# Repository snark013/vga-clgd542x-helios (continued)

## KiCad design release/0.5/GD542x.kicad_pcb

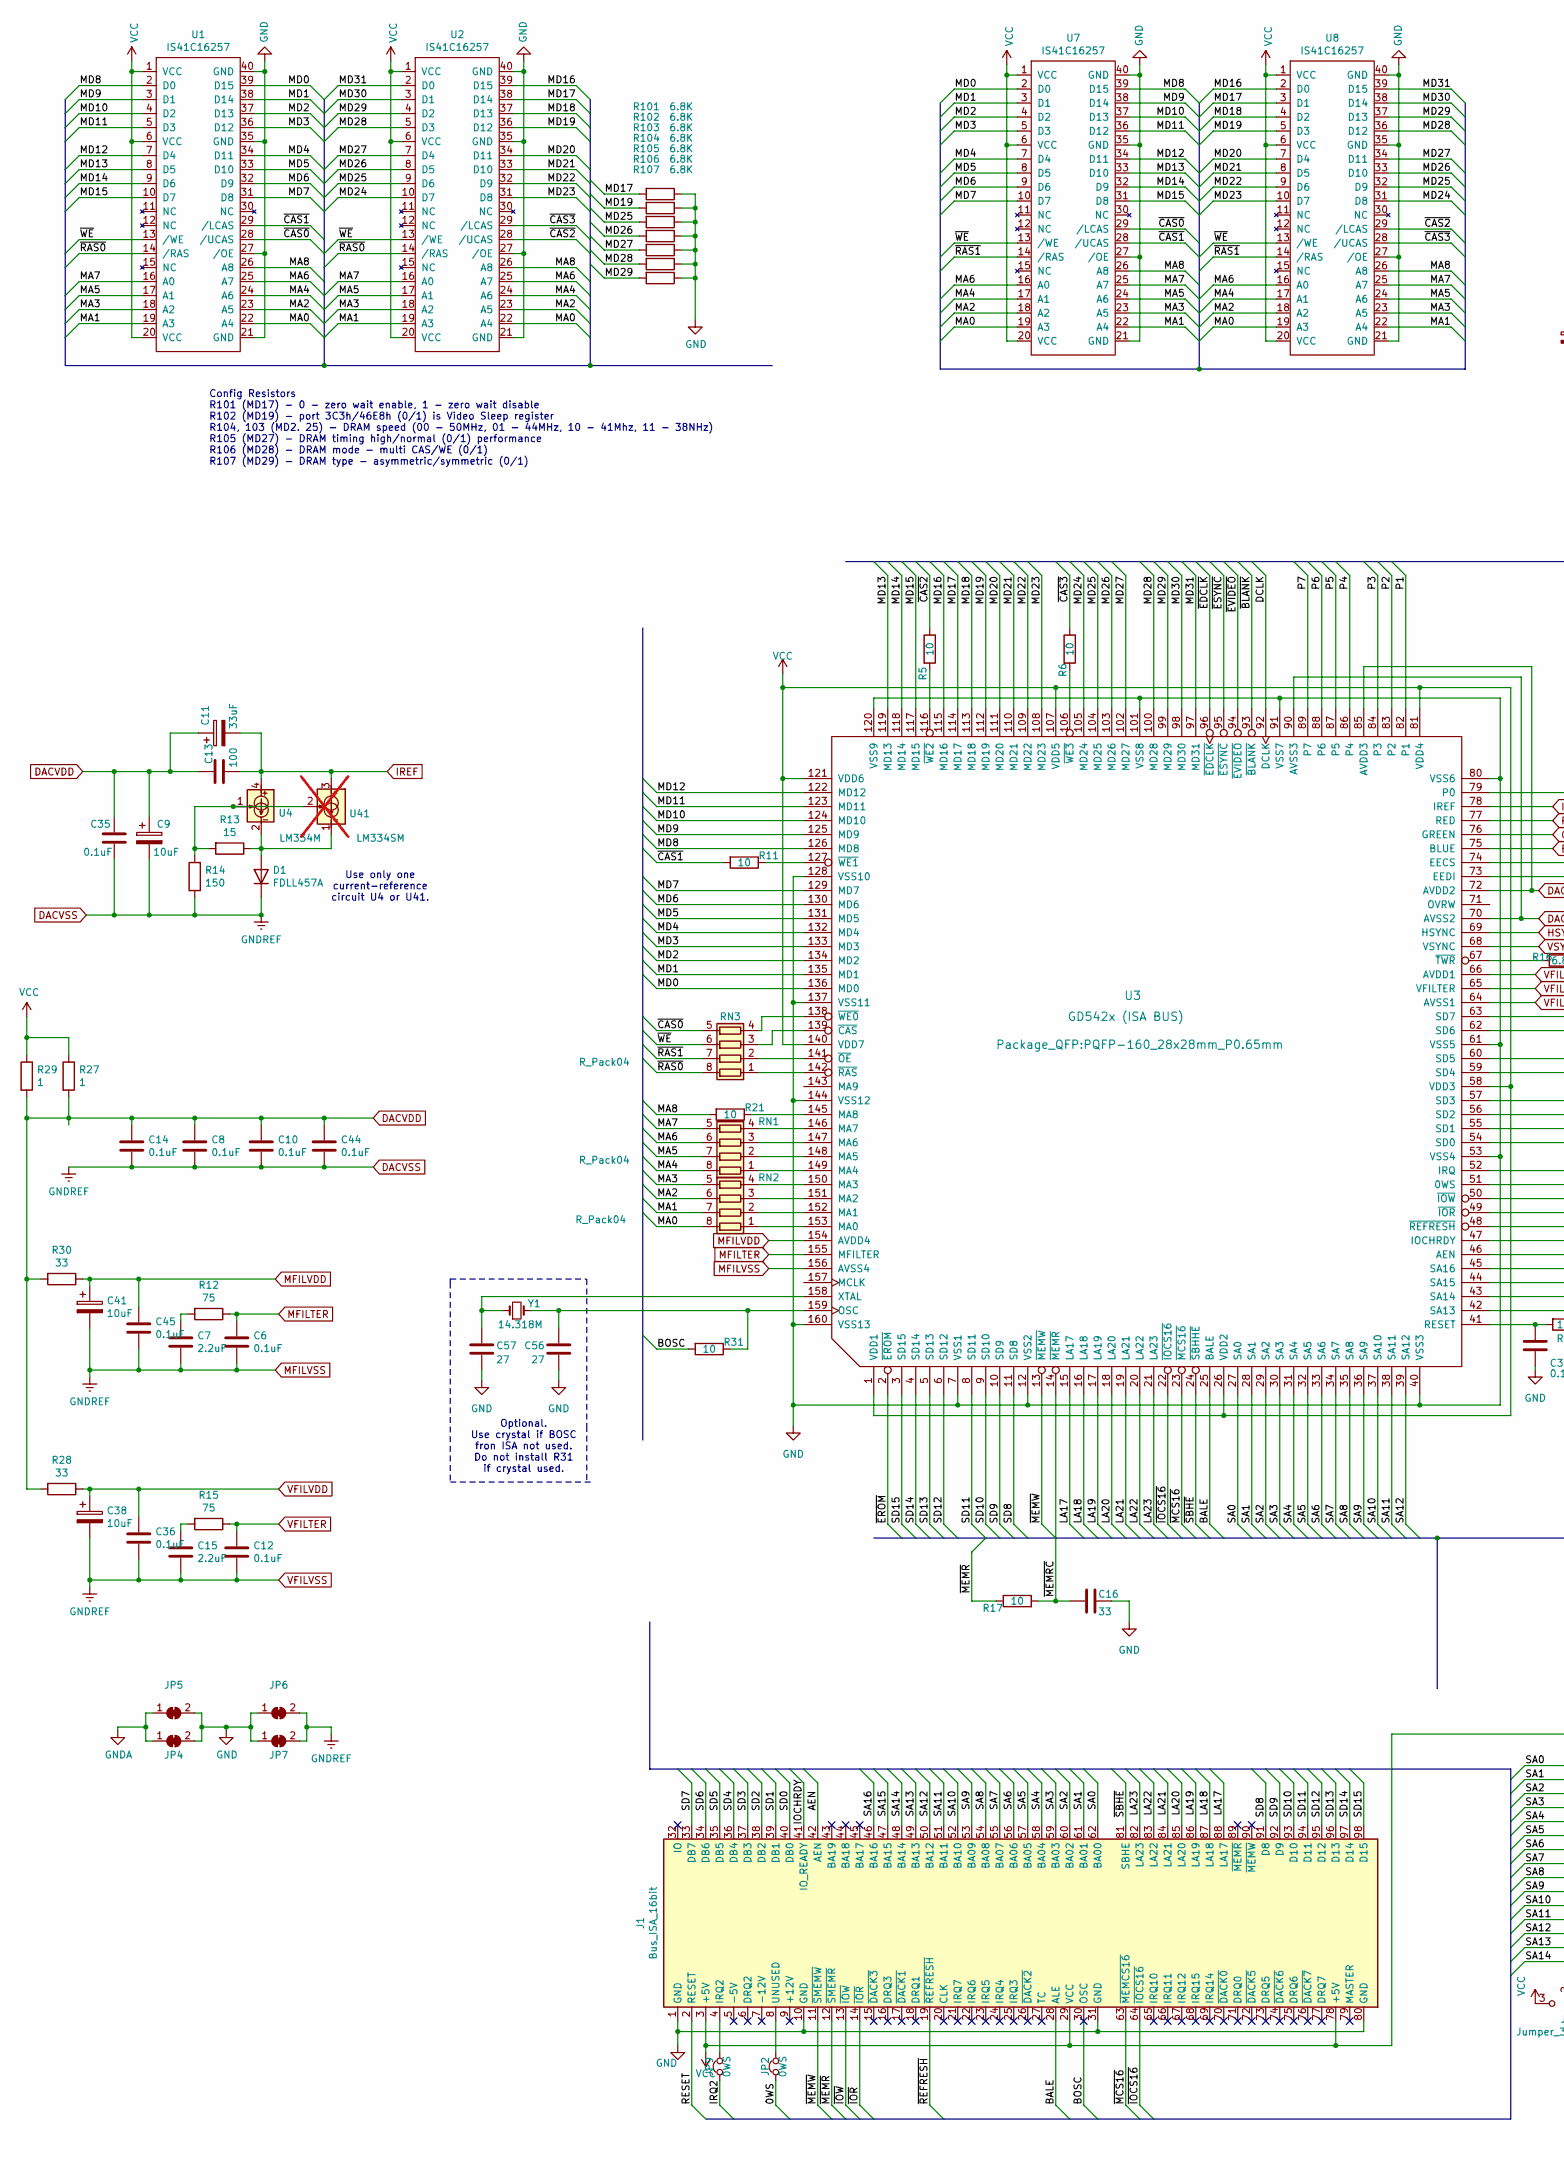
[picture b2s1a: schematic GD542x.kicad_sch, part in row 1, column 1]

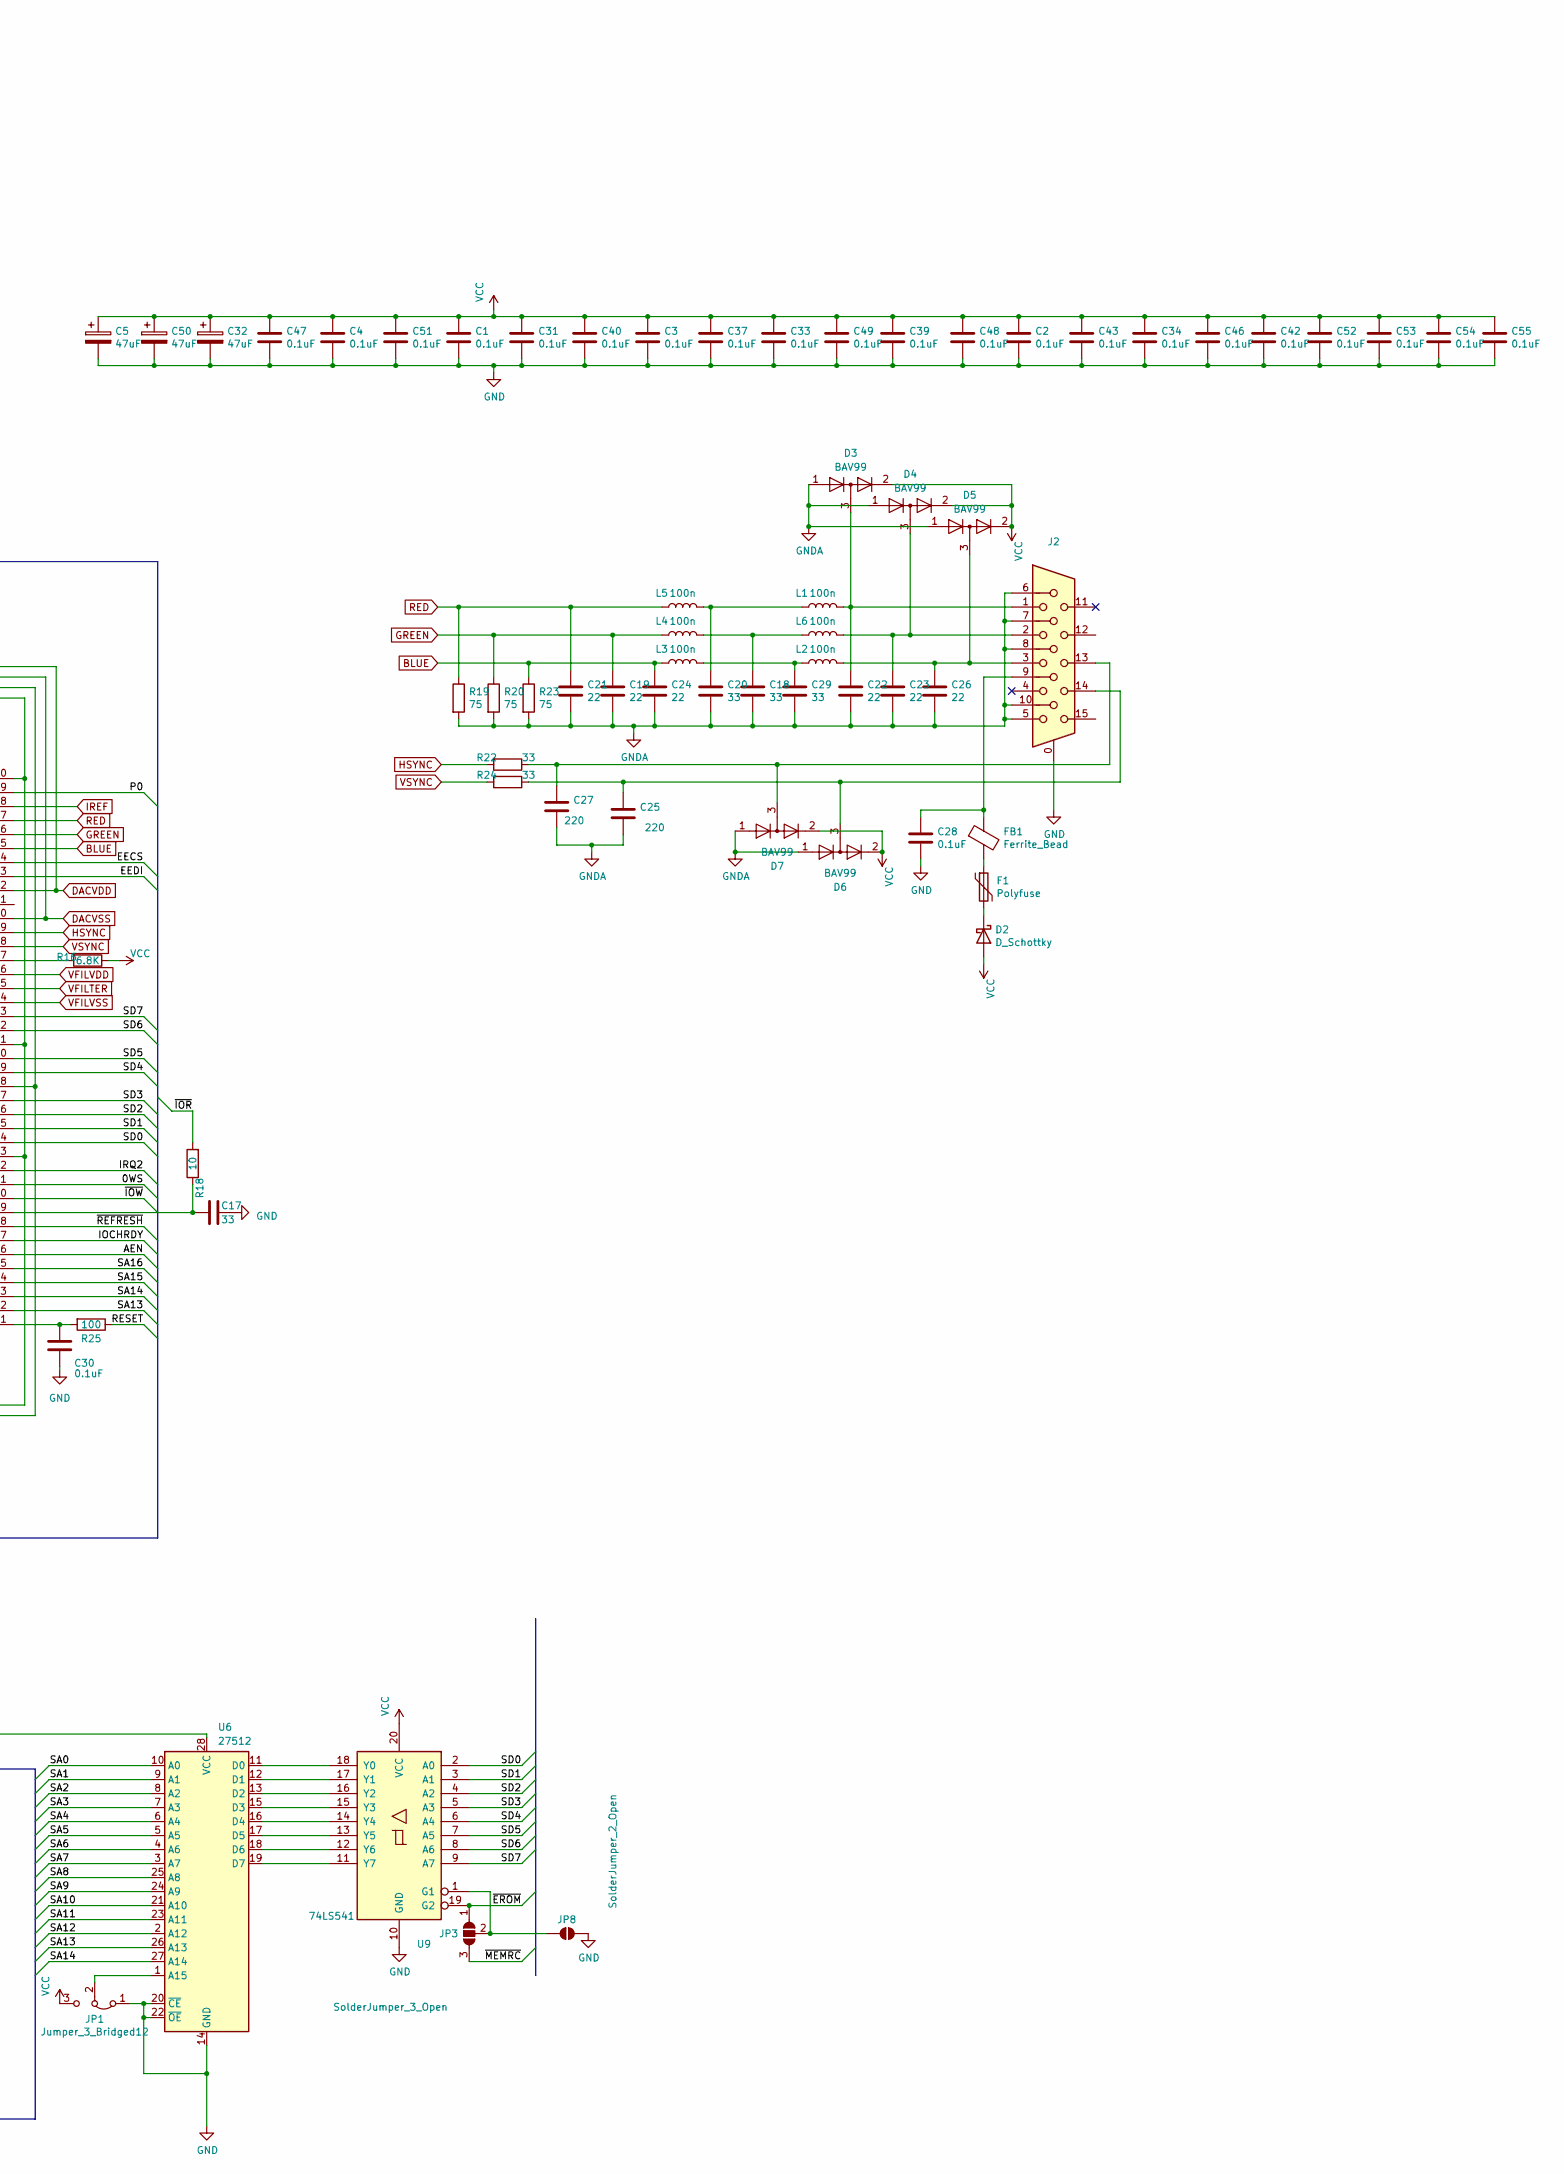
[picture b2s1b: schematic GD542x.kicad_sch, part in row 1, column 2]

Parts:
C1, C2, C3, C4, C6, C8, C10, C12, C14, C28, C30, C31, C33, C34, C35, C36, C37, C39, C40, C42, C43, C44, C45, C46, C47, C48, C49, C51, C52, C53, C54, C55: 0.1uF; C_0603_1608Metric
C5, C32, C50: 47uF; CP_EIA-3216-18_Kemet-A
C7, C15: 2.2uF; C_0603_1608Metric
C9: 10uF; CP_EIA-3216-18_Kemet-A
C11: 33uF; CP_EIA-3216-18_Kemet-A
C13: 100; C_0603_1608Metric
C16, C17, C18, C20, C29: 33; C_0603_1608Metric
C19, C21, C22, C23, C24, C26: 22; C_0603_1608Metric
C25, C27: 220; C_0603_1608Metric
C38, C41: 10uF; CP_EIA-3216-18_Kemet-A_Pad1.58x1.35mm_HandSolder
C56, C57: 27; C_0603_1608Metric
D1: FDLL457A; D_MiniMELF_Handsoldering
D2: D_Schottky; D_MELF-RM10_Universal_Handsoldering
D3, D4, D5, D6, D7: BAV99; SOT-23
F1: Polyfuse; Fuse_0805_2012Metric_Pad1.15x1.40mm_HandSolder
FB1: Ferrite_Bead; L_0805_2012Metric_Pad1.15x1.40mm_HandSolder
J1: Bus_ISA_16bit; BUS_AT
J2: DB15_Female_HighDensity_MountingHoles; DSUB-15-HD_Female_Horizontal_P2.29x1.98mm_EdgePinOffset3.03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
JP1: Jumper_3_Bridged12; PinHeader_1x03_P2.54mm_Vertical
JP2, JP9: 0WS; PinHeader_1x02_P2.54mm_Vertical
JP3: SolderJumper_3_Open; SolderJumper-3_P1.3mm_Open_RoundedPad1.0x1.5mm
JP4, JP5, JP6, JP7: SolderJumper_2_Bridged; NonSolderJumper-2_P1.3mm_Bridged2Bar_Pad1.0x1.5mm
JP8: SolderJumper_2_Open; SolderJumper-2_P1.3mm_Open_RoundedPad1.0x1.5mm
L1, L2, L3, L4, L5, L6: 100n; L_0805_2012Metric_Pad1.15x1.40mm_HandSolder
R5, R6, R11, R21: 10; R_0402_1005Metric_Pad0.72x0.64mm_HandSolder
R12, R15, R19, R20, R23: 75; R_0603_1608Metric
R13: 15; R_0603_1608Metric
R14: 150; R_0603_1608Metric
R16, R101, R102, R103, R104, R105, R106, R107: 6.8K; R_0603_1608Metric
R17, R18, R31: 10; R_0603_1608Metric
R22, R24, R28, R30: 33; R_0603_1608Metric
R25: 100; R_0603_1608Metric
R27, R29: 1; R_0603_1608Metric
RN1, RN2, RN3: R_Pack04; R_Array_Concave_4x0603
U1, U2, U7, U8: IS41C16257; SOJ-40-Socket-LongPads
U3: GD542x (ISA BUS); PQFP-160_28x28mm_P0.65mm
U4: LM334M; SOIC-8_3.9x4.9mm_P1.27mm
U6: 27512; DIP-28_W15.24mm
U9: 74LS541; CERDIP-20_W7.62mm_SideBrazed
U41: LM334SM; SOIC-8_3.9x4.9mm_P1.27mm; not fitted
Y1: 14.318M; Crystal_SMD_5032-2Pin_5.0x3.2mm_HandSoldering

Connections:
/0WS: JP2.1, U3.51 (0WS)
/AEN: J1.42 (AEN), U3.46 (AEN)
/BALE: J1.28 (ALE), U3.25 (BALE)
/BOSC: J1.30 (OSC), R31.2
/DCLK: U3.92 (DCLK)
/EECS: U3.74 (EECS)
/EEDI: U3.73 (EEDI)
/IOCHRDY: J1.41 (IO_READY), U3.47 (IOCHRDY)
/IRQ2: JP9.1, U3.52 (IRQ)
/LA17: J1.88 (LA17), U3.15 (LA17)
/LA18: J1.87 (LA18), U3.16 (LA18)
/LA19: J1.86 (LA19), U3.17 (LA19)
/LA20: J1.85 (LA20), U3.18 (LA20)
/LA21: J1.84 (LA21), U3.19 (LA21)
/LA22: J1.83 (LA22), U3.20 (LA22)
/LA23: J1.82 (LA23), U3.21 (LA23)
/MA0: RN2.8 (R1.2), U1.22 (A4), U2.22 (A4), U7.19 (A3), U8.19 (A3)
/MA1: RN2.7 (R2.2), U1.19 (A3), U2.19 (A3), U7.22 (A4), U8.22 (A4)
/MA2: RN2.6 (R3.2), U1.23 (A5), U2.23 (A5), U7.18 (A2), U8.18 (A2)
/MA3: RN2.5 (R4.2), U1.18 (A2), U2.18 (A2), U7.23 (A5), U8.23 (A5)
/MA4: RN1.8 (R1.2), U1.24 (A6), U2.24 (A6), U7.17 (A1), U8.17 (A1)
/MA5: RN1.7 (R2.2), U1.17 (A1), U2.17 (A1), U7.24 (A6), U8.24 (A6)
/MA6: RN1.6 (R3.2), U1.25 (A7), U2.25 (A7), U7.16 (A0), U8.16 (A0)
/MA7: RN1.5 (R4.2), U1.16 (A0), U2.16 (A0), U7.25 (A7), U8.25 (A7)
/MA8: R21.2, U1.26 (A8), U2.26 (A8), U7.26 (A8), U8.26 (A8)
/MD0: U1.39 (D15), U3.136 (MD0), U7.2 (D0)
/MD1: U1.38 (D14), U3.135 (MD1), U7.3 (D1)
/MD2: U1.37 (D13), U3.134 (MD2), U7.4 (D2)
/MD3: U1.36 (D12), U3.133 (MD3), U7.5 (D3)
/MD4: U1.34 (D11), U3.132 (MD4), U7.7 (D4)
/MD5: U1.33 (D10), U3.131 (MD5), U7.8 (D5)
/MD6: U1.32 (D9), U3.130 (MD6), U7.9 (D6)
/MD7: U1.31 (D8), U3.129 (MD7), U7.10 (D7)
/MD8: U1.2 (D0), U3.126 (MD8), U7.39 (D15)
/MD9: U1.3 (D1), U3.125 (MD9), U7.38 (D14)
/MD10: U1.4 (D2), U3.124 (MD10), U7.37 (D13)
/MD11: U1.5 (D3), U3.123 (MD11), U7.36 (D12)
/MD12: U1.7 (D4), U3.122 (MD12), U7.34 (D11)
/MD13: U1.8 (D5), U3.119 (MD13), U7.33 (D10)
/MD14: U1.9 (D6), U3.118 (MD14), U7.32 (D9)
/MD15: U1.10 (D7), U3.117 (MD15), U7.31 (D8)
/MD16: U2.39 (D15), U3.115 (MD16), U8.2 (D0)
/MD17: R101.2, U2.38 (D14), U3.114 (MD17), U8.3 (D1)
/MD18: U2.37 (D13), U3.113 (MD18), U8.4 (D2)
/MD19: R102.2, U2.36 (D12), U3.112 (MD19), U8.5 (D3)
/MD20: U2.34 (D11), U3.111 (MD20), U8.7 (D4)
/MD21: U2.33 (D10), U3.110 (MD21), U8.8 (D5)
/MD22: U2.32 (D9), U3.109 (MD22), U8.9 (D6)
/MD23: U2.31 (D8), U3.108 (MD23), U8.10 (D7)
/MD24: U2.10 (D7), U3.105 (MD24), U8.31 (D8)
/MD25: R103.2, U2.9 (D6), U3.104 (MD25), U8.32 (D9)
/MD26: R104.2, U2.8 (D5), U3.103 (MD26), U8.33 (D10)
/MD27: R105.2, U2.7 (D4), U3.102 (MD27), U8.34 (D11)
/MD28: R106.2, U2.5 (D3), U3.100 (MD28), U8.36 (D12)
/MD29: R107.2, U2.4 (D2), U3.99 (MD29), U8.37 (D13)
/MD30: U2.3 (D1), U3.98 (MD30), U8.38 (D14)
/MD31: U2.2 (D0), U3.97 (MD31), U8.39 (D15)
/P0: U3.79 (P0)
/P1: U3.82 (P1)
/P2: U3.83 (P2)
/P3: U3.84 (P3)
/P4: U3.86 (P4)
/P5: U3.87 (P5)
/P6: U3.88 (P6)
/P7: U3.89 (P7)
/RESET: J1.2 (RESET), R25.1
/SA0: J1.62 (BA00), U3.27 (SA0), U6.10 (A0)
/SA1: J1.61 (BA01), U3.28 (SA1), U6.9 (A1)
/SA2: J1.60 (BA02), U3.29 (SA2), U6.8 (A2)
/SA3: J1.59 (BA03), U3.30 (SA3), U6.7 (A3)
/SA4: J1.58 (BA04), U3.31 (SA4), U6.6 (A4)
/SA5: J1.57 (BA05), U3.32 (SA5), U6.5 (A5)
/SA6: J1.56 (BA06), U3.33 (SA6), U6.4 (A6)
/SA7: J1.55 (BA07), U3.34 (SA7), U6.3 (A7)
/SA8: J1.54 (BA08), U3.35 (SA8), U6.25 (A8)
/SA9: J1.53 (BA09), U3.36 (SA9), U6.24 (A9)
/SA10: J1.52 (BA10), U3.37 (SA10), U6.21 (A10)
/SA11: J1.51 (BA11), U3.38 (SA11), U6.23 (A11)
/SA12: J1.50 (BA12), U3.39 (SA12), U6.2 (A12)
/SA13: J1.49 (BA13), U3.42 (SA13), U6.26 (A13)
/SA14: J1.48 (BA14), U3.43 (SA14), U6.27 (A14)
/SA15: J1.47 (BA15), U3.44 (SA15)
/SA16: J1.46 (BA16), U3.45 (SA16)
/SD0: J1.40 (DB0), U3.54 (SD0), U9.2 (A0)
/SD1: J1.39 (DB1), U3.55 (SD1), U9.3 (A1)
/SD2: J1.38 (DB2), U3.56 (SD2), U9.4 (A2)
/SD3: J1.37 (DB3), U3.57 (SD3), U9.5 (A3)
/SD4: J1.36 (DB4), U3.59 (SD4), U9.6 (A4)
/SD5: J1.35 (DB5), U3.60 (SD5), U9.7 (A5)
/SD6: J1.34 (DB6), U3.62 (SD6), U9.8 (A6)
/SD7: J1.33 (DB7), U3.63 (SD7), U9.9 (A7)
/SD8: J1.91 (D8), U3.11 (SD8)
/SD9: J1.92 (D9), U3.10 (SD9)
/SD10: J1.93 (D10), U3.9 (SD10)
/SD11: J1.94 (D11), U3.8 (SD11)
/SD12: J1.95 (D12), U3.6 (SD12)
/SD13: J1.96 (D13), U3.5 (SD13)
/SD14: J1.97 (D14), U3.4 (SD14)
/SD15: J1.98 (D15), U3.3 (SD15)
/~BLANK: U3.93 (~BLANK)
/~CAS0: RN3.5 (R4.2), U1.28 (/UCAS), U7.29 (/LCAS)
/~CAS1: R11.2, U1.29 (/LCAS), U7.28 (/UCAS)
/~CAS2: R5.1, U2.28 (/UCAS), U8.29 (/LCAS)
/~CAS3: R6.1, U2.29 (/LCAS), U8.28 (/UCAS)
/~EDCLK: U3.96 (~EDCLK)
/~EROM: JP3.1 (A), U3.2 (~EROM), U9.19 (G2)
/~ESYNC: U3.95 (~ESYNC)
/~EVIDEO: U3.94 (~EVIDEO)
/~IOCS16: J1.64 (~IOCS16), U3.22 (~IOCS16)
/~IOR: J1.14 (~IOR), R18.2
/~IOW: J1.13 (~IOW), U3.50 (~IOW)
/~MCS16: J1.63 (~MEMCS16), U3.23 (~MCS16)
/~MEMRC: C16.2, JP3.3 (B), R17.2, U3.14 (~MEMR)
/~MEMR: J1.12 (~SMEMR), R17.1
/~MEMW: J1.11 (~SMEMW), U3.13 (~MEMW)
/~RAS0: RN3.8 (R1.2), U1.14 (/RAS), U2.14 (/RAS)
/~RAS1: RN3.7 (R2.2), U7.14 (/RAS), U8.14 (/RAS)
/~REFRESH: J1.19 (~REFRESH), U3.48 (~REFRESH)
/~SBHE: J1.81 (SBHE), U3.24 (~SBHHE)
/~WE: RN3.6 (R3.2), U1.13 (/WE), U2.13 (/WE), U7.13 (/WE), U8.13 (/WE)
BLUE: C24.1, L3.1, R23.1, U3.75 (BLUE)
DACVDD: C8.1, C9.1, C10.1, C11.1, C13.1, C14.1, C35.1, C44.1, R27.2, R28.2, R29.2, R30.2, U3.72 (AVDD2), U3.85 (AVDD3)
DACVSS: C6.2, C7.2, C8.2, C9.2, C10.2, C12.2, C14.2, C15.2, C35.2, C36.2, C38.2, C41.2, C44.2, C45.2, D1.1 (K), JP6.2 (B), JP7.2 (B), R14.1, U3.64 (AVSS1), U3.70 (AVSS2), U3.90 (AVSS3), U3.156 (AVSS4)
GND: C1.2, C2.2, C3.2, C4.2, C5.2, C16.1, C17.1, C28.2, C30.2, C31.2, C32.2, C33.2, C34.2, C37.2, C39.2, C40.2, C42.2, C43.2, C46.2, C47.2, C48.2, C49.2, C50.2, C51.2, C52.2, C53.2, C54.2, C55.2, C56.2, C57.2, J1.1 (GND), J1.10 (GND), J1.31 (GND), J1.80 (GND), J2.0, JP1.1 (A), JP4.2 (B), JP5.2 (B), JP6.1 (A), JP7.1 (A), JP8.1 (A), R101.1, R102.1, R103.1, R104.1, R105.1, R106.1, R107.1, U1.21 (GND), U1.27 (/OE), U1.35 (GND), U1.40 (GND), U2.21 (GND), U2.27 (/OE), U2.35 (GND), U2.40 (GND), U3.7 (VSS1), U3.12 (VSS2), U3.40 (VSS3), U3.53 (VSS4), U3.61 (VSS5), U3.80 (VSS6), U3.91 (VSS7), U3.101 (VSS8), U3.120 (VSS9), U3.128 (VSS10), U3.137 (VSS11), U3.144 (VSS12), U3.160 (VSS13), U6.14 (GND), U6.20 (~CE), U6.22 (~OE), U7.21 (GND), U7.27 (/OE), U7.35 (GND), U7.40 (GND), U8.21 (GND), U8.27 (/OE), U8.35 (GND), U8.40 (GND), U9.10 (GND)
GNDA: C18.2, C19.2, C20.2, C21.2, C22.2, C23.2, C24.2, C25.2, C26.2, C27.2, C29.2, D3.1 (K), D4.1 (K), D5.1 (K), D6.1 (K), D7.1 (K), J2.5, J2.6, J2.7, J2.8, J2.10, JP4.1 (A), JP5.1 (A), R19.2, R20.2, R23.2
GREEN: C19.1, L4.1, R20.1, U3.76 (GREEN)
HSYNC: R22.2, U3.69 (HSYNC)
IREF: C11.2, C13.2, U3.78 (IREF), U4.4, U41.3
MFILTER: C6.1, R12.1, U3.155 (MFILTER)
MFILVDD: C41.1, C45.1, R30.1, U3.154 (AVDD4)
unnamed: C7.1, R12.2
unnamed: C15.1, R15.2
unnamed: C18.1, L4.2, L6.1
unnamed: C20.1, L1.1, L5.2
unnamed: C22.1, D3.3 (K), J2.1, L1.2
unnamed: C23.1, D4.3 (K), J2.2, L6.2
unnamed: C25.1, D6.3 (K), J2.14, R24.1
unnamed: C26.1, D5.3 (K), J2.3, L2.2
unnamed: C27.1, D7.3 (K), J2.13, R22.1
unnamed: C28.1, FB1.1, J2.9
unnamed: C29.1, L2.1, L3.2
unnamed: D1.2 (A), R13.1, U4.2, U4.3, U4.6, U4.7, U41.1
unnamed: D2.1 (K), F1.2
unnamed: F1.1, FB1.2
unnamed: J1.4 (IRQ2), JP9.2
unnamed: J1.8 (UNUSED), JP2.2
unnamed: JP1.2 (C), U6.1 (A15)
unnamed: JP3.2 (C), JP8.2 (B), U9.1 (G1)
unnamed: R13.2, R14.2, U4.1, U41.2
unnamed: RN1.1 (R1.1), U3.149 (MA4)
unnamed: RN1.2 (R2.1), U3.148 (MA5)
unnamed: RN1.3 (R3.1), U3.147 (MA6)
unnamed: RN1.4 (R4.1), U3.146 (MA7)
unnamed: RN2.1 (R1.1), U3.153 (MA0)
unnamed: RN2.2 (R2.1), U3.152 (MA1)
unnamed: RN2.3 (R3.1), U3.151 (MA2)
unnamed: RN2.4 (R4.1), U3.150 (MA3)
unnamed: RN3.1 (R1.1), U3.142 (~RAS)
unnamed: RN3.2 (R2.1), U3.141 (~OE)
unnamed: RN3.3 (R3.1), U3.139 (~CAS)
unnamed: RN3.4 (R4.1), U3.138 (~WE0)
unnamed: R21.1, U3.145 (MA8)
unnamed: C56.1, R31.1, U3.159 (OSC), Y1.2
unnamed: C30.1, R25.2, U3.41 (RESET)
unnamed: C57.1, U3.158 (XTAL), Y1.1
unnamed: C17.2, R18.1, U3.49 (~IOR)
unnamed: R16.2, U3.67 (~TWR)
unnamed: R11.1, U3.127 (~WE1)
unnamed: R5.2, U3.116 (~WE2)
unnamed: R6.2, U3.106 (~WE3)
unnamed: U6.11 (D0), U9.18 (Y0)
unnamed: U6.12 (D1), U9.17 (Y1)
unnamed: U6.13 (D2), U9.16 (Y2)
unnamed: U6.15 (D3), U9.15 (Y3)
unnamed: U6.16 (D4), U9.14 (Y4)
unnamed: U6.17 (D5), U9.13 (Y5)
unnamed: U6.18 (D6), U9.12 (Y6)
unnamed: U6.19 (D7), U9.11 (Y7)
RED: C21.1, L5.1, R19.1, U3.77 (RED)
VCC: C1.1, C2.1, C3.1, C4.1, C5.1, C31.1, C32.1, C33.1, C34.1, C37.1, C39.1, C40.1, C42.1, C43.1, C46.1, C47.1, C48.1, C49.1, C50.1, C51.1, C52.1, C53.1, C54.1, C55.1, D2.2 (A), D3.2 (A), D4.2 (A), D5.2 (A), D6.2 (A), D7.2 (A), J1.3 (+5V), J1.29 (VCC), J1.78 (+5V), JP1.3 (B), R16.1, R27.1, R29.1, U1.1 (VCC), U1.6 (VCC), U1.20 (VCC), U2.1 (VCC), U2.6 (VCC), U2.20 (VCC), U3.1 (VDD1), U3.26 (VDD2), U3.58 (VDD3), U3.81 (VDD4), U3.107 (VDD5), U3.121 (VDD6), U3.140 (VDD7), U6.28 (VCC), U7.1 (VCC), U7.6 (VCC), U7.20 (VCC), U8.1 (VCC), U8.6 (VCC), U8.20 (VCC), U9.20 (VCC)
VFILTER: C12.1, R15.1, U3.65 (VFILTER)
VFILVDD: C36.1, C38.1, R28.1, U3.66 (AVDD1)
VSYNC: R24.2, U3.68 (VSYNC)

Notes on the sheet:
Config Resistors R101 (MD17) - 0 - zero wait enable, 1 - zero wait disable R102 (MD19) - port 3C3h/46E8h (0/1) is Video Sleep register R104, 103 (MD2. 25) - DRAM speed (00 - 50MHz, 01 - 44MHz, 10 - 41Mhz, 11 - 38NHz) R105 (MD27) - DRAM timing high/normal (0/1) performance R106 (MD28) - DRAM mode - 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
Optional. Use crystal if BOSC fron ISA not used. Do not install R31 if crystal used.
Use only one current-reference circuit U4 or U41.

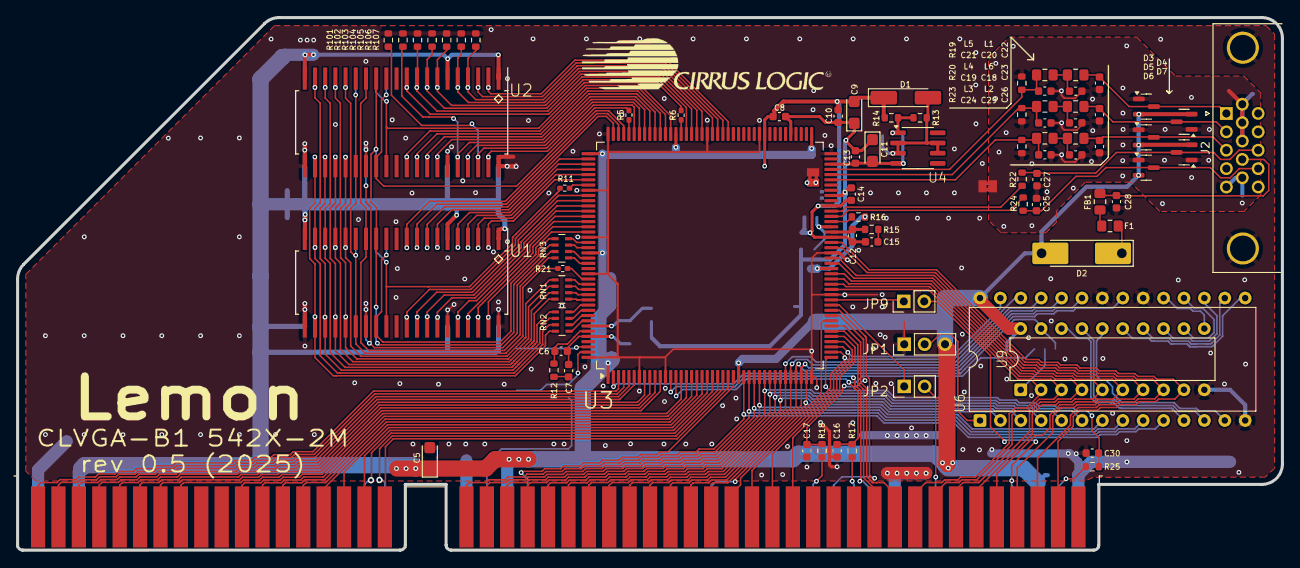
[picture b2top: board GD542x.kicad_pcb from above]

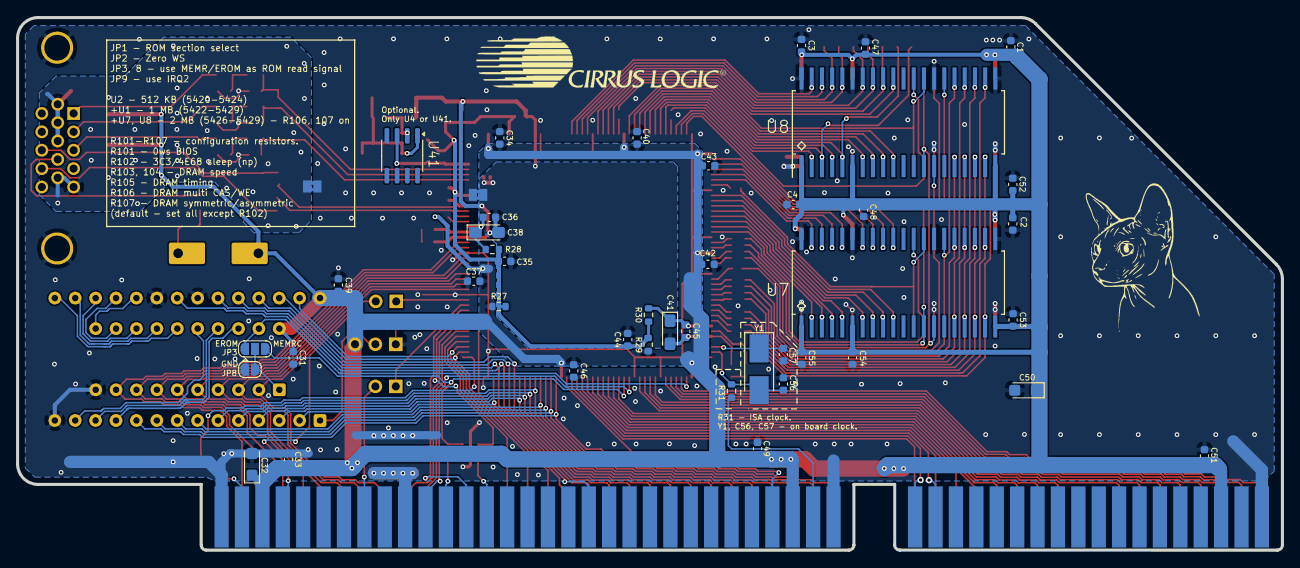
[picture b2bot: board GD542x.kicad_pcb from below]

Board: 2 copper layers, 157.5 x 66.3 mm, 125 parts (44 on the bottom side), 168 nets.

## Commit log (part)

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2025-09-13 Initial build.
2025-09-13 Обновить README.md
2025-09-13 ChangeLog: - some structure optimization.
2025-09-13 ChangeLog: - release 1.2.5
2025-09-13 docs added.
2025-09-13 ChangeLog: - 1.2.5 release.
2025-09-13 release files update.
2025-09-13 Release 1.2.5
2025-09-14 ChangeLog: - add lost sphynx logo.
